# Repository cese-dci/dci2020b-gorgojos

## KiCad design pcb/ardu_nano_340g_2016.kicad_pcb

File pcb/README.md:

Directorio “pcb” donde se colocará el proyecto Kicad.

se agregan librerias de digikey y de https://github.com/epernia/CIAA-Z3R0

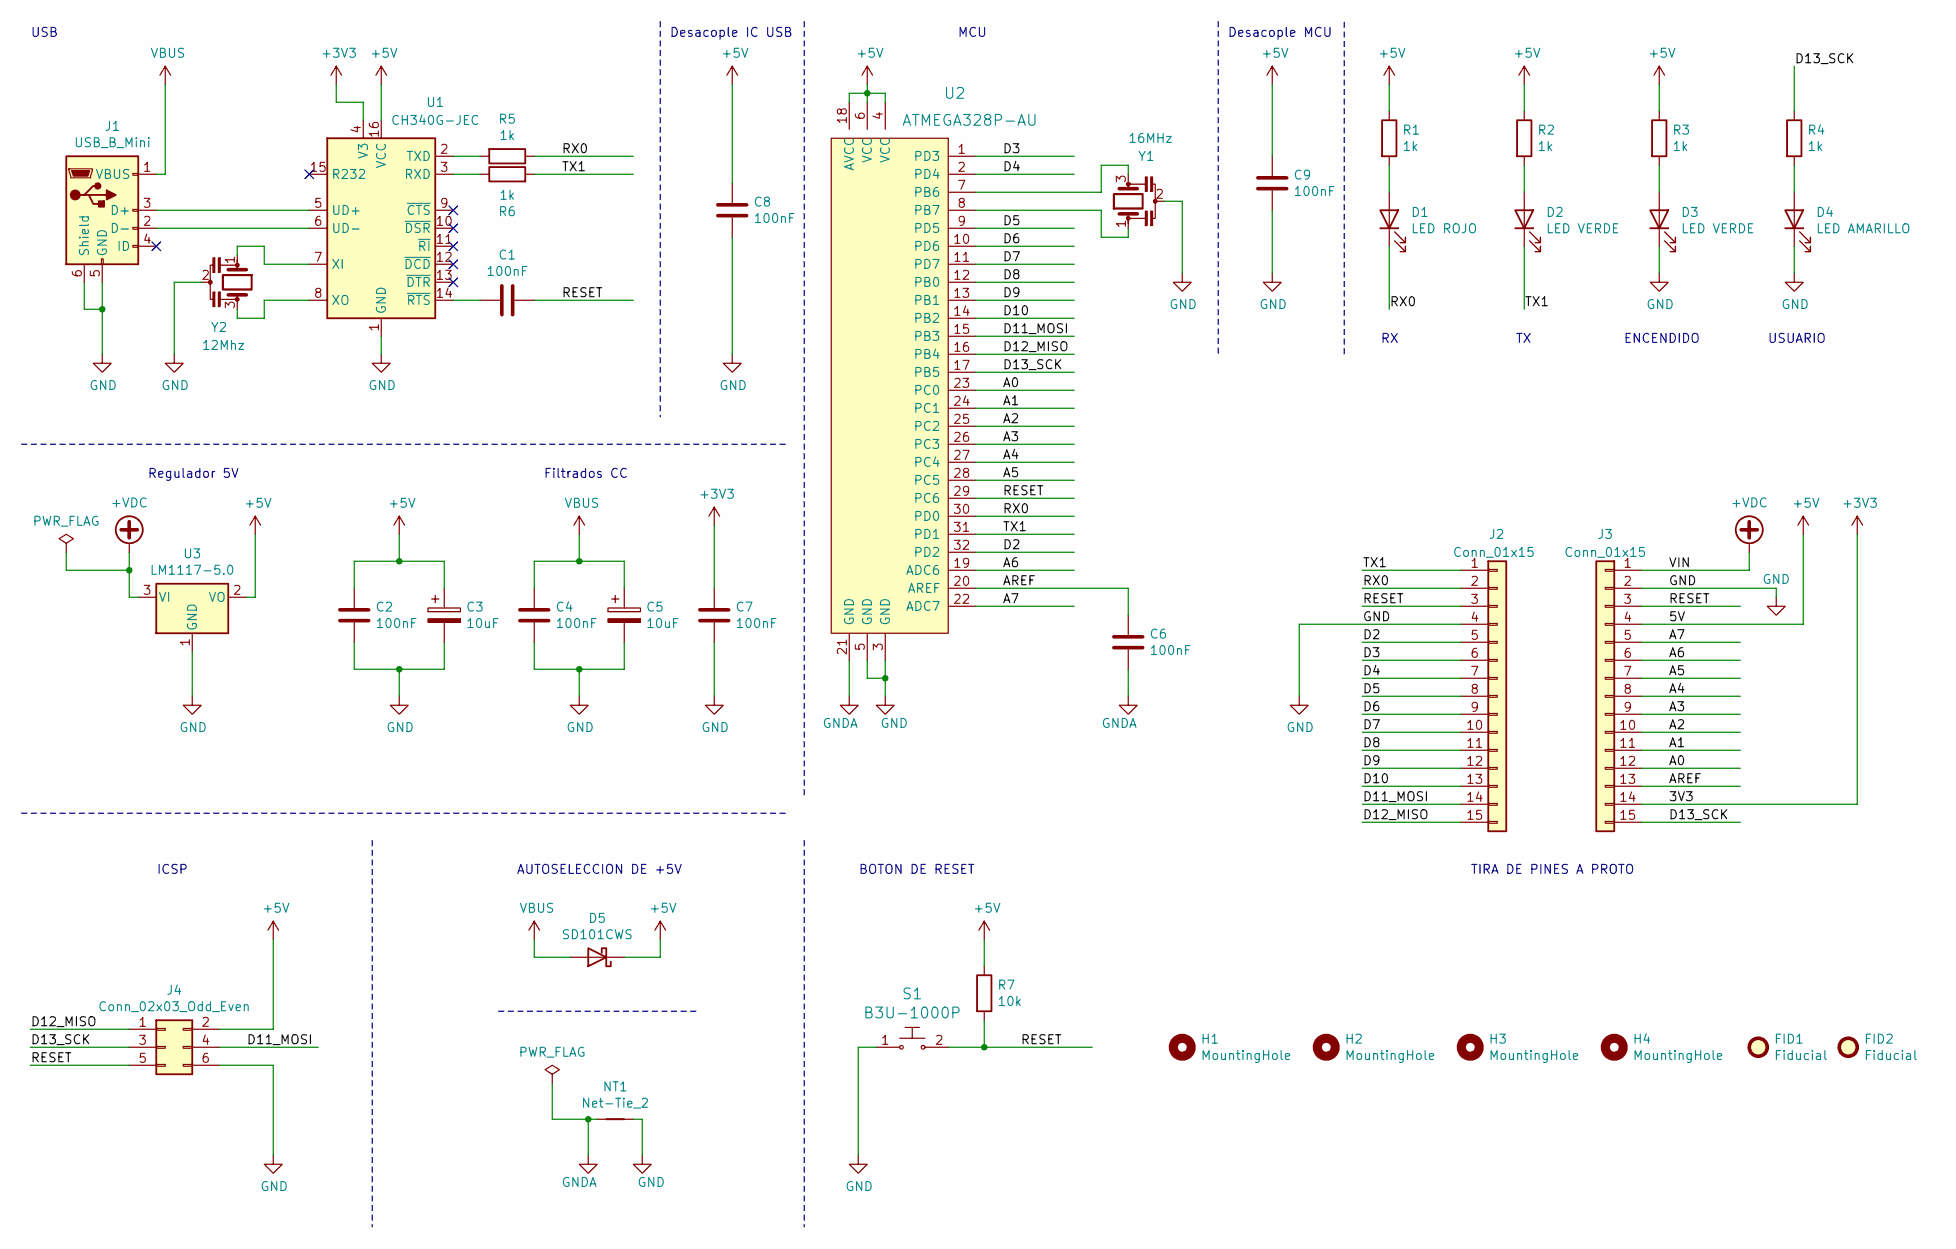
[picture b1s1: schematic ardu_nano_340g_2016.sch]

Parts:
C1, C2, C4, C6: 100nF; C_0805_2012Metric_Pad1.15x1.40mm_HandSolder; MPN CL21B104KBFXPJE; Digi-Key_PN 1276-CL21B104KBFXPJECT-ND
C3, C5: 10uF; CP_EIA-3216-18_Kemet-A_Pad1.58x1.35mm_HandSolder; Digi-Key_PN C194304
C7, C8, C9: 100nF; C_0805_2012Metric_Pad1.18x1.45mm_HandSolder; MPN CL21B104KBFXPJE; Digi-Key_PN 1276-CL21B104KBFXPJECT-ND
D1: LED ROJO; LED_0805_2012Metric_Pad1.15x1.40mm_HandSolder; MPN 150080SS75000; Digi-Key_PN 732-4985-1-ND
D2, D3: LED VERDE; LED_0805_2012Metric_Pad1.15x1.40mm_HandSolder; MPN 150080VS75000; Digi-Key_PN 732-4986-1-ND
D4: LED AMARILLO; LED_0805_2012Metric_Pad1.15x1.40mm_HandSolder; MPN 150080YS75000; Digi-Key_PN 732-4987-1-ND
D5: SD101CWS; D_SOD-323_HandSoldering; MPN SD101CWS; Digi-Key_PN C241955
FID1, FID2: Fiducial; Fiducial_1mm_Mask2mm
H1, H2: MountingHole; MountingHole_2.2mm_M2_ISO7380
H3, H4: MountingHole; MountingHole_2.2mm_M2_ISO14580
J1: USB_B_Mini; USB_Mini-B_Lumberg_2486_01_Horizontal; MPN UX60-MB-5ST; Digi-Key_PN H2959CT-ND
J2, J3: Conn_01x15; PinHeader_1x15_P2.54mm_Vertical; MPN TSW-115-07-T-S; Digi-Key_PN SAM1035-15-ND
J4: Conn_02x03_Odd_Even; PinHeader_2x03_P2.54mm_Vertical; MPN TSW-103-07-T-D; Digi-Key_PN SAM1034-03-ND
NT1: Net-Tie_2; NetTie-2_SMD_Pad0.5mm
R1, R2, R3, R4, R5, R6: 1k; R_0805_2012Metric_Pad1.15x1.40mm_HandSolder; MPN RNCP0805FTD1K00; Digi-Key_PN RNCP0805FTD1K00CT-ND
R7: 10k; R_0805_2012Metric_Pad1.15x1.40mm_HandSolder; MPN RNCP0805FTD1K00; Digi-Key_PN RNCP0805FTD1K00CT-ND
S1: B3U-1000P; Switch_Tactile_SMD_B3U-1000P; MPN B3U-1000P; Digi-Key_PN SW1020CT-ND
U1: CH340G-JEC; SOIC-16_3.9x9.9mm_P1.27mm; MPN CH340G; Digi-Key_PN C14267
U2: ATMEGA328P-AU; LQFP-32_7x7mm_P0.8mm; MPN ATMEGA328P-AU; Digi-Key_PN ATMEGA328P-AU-ND
U3: LM1117-5.0; SOT-223-3_TabPin2; MPN LM1117MP-5.0/NOPB; Digi-Key_PN LM1117MP-5.0/NOPBCT-ND
Y1: 16MHz; Resonator_SMD_muRata_CSTxExxV-3Pin_3.0x1.1mm; MPN CSTNE16M0V530000R0; Digi-Key_PN 490-17948-1-ND
Y2: 12Mhz; Resonator_SMD_muRata_CSTxExxV-3Pin_3.0x1.1mm; MPN CSTNE12M0G550000R0; Digi-Key_PN 490-17943-1-ND

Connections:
+3V3: C7.1, J3.14, U1.4 (V3)
+5V: C2.1, C3.1, C8.1, C9.1, D5.1 (K), J3.4, J4.2, R1.1, R2.1, R3.1, R7.1, U1.16 (VCC), U2.4 (VCC), U2.6 (VCC), U2.18 (AVCC), U3.2 (VO)
+VDC: J3.1, U3.3 (VI)
/A0: J3.12, U2.23 (PC0)
/A1: J3.11, U2.24 (PC1)
/A2: J3.10, U2.25 (PC2)
/A3: J3.9, U2.26 (PC3)
/A4: J3.8, U2.27 (PC4)
/A5: J3.7, U2.28 (PC5)
/A6: J3.6, U2.19 (ADC6)
/A7: J3.5, U2.22 (ADC7)
/AREF: C6.1, J3.13, U2.20 (AREF)
/D2: J2.5, U2.32 (PD2)
/D3: J2.6, U2.1 (PD3)
/D4: J2.7, U2.2 (PD4)
/D5: J2.8, U2.9 (PD5)
/D6: J2.9, U2.10 (PD6)
/D7: J2.10, U2.11 (PD7)
/D8: J2.11, U2.12 (PB0)
/D9: J2.12, U2.13 (PB1)
/D10: J2.13, U2.14 (PB2)
/D11_MOSI: J2.14, J4.4, U2.15 (PB3)
/D12_MISO: J2.15, J4.1, U2.16 (PB4)
/D13_SCK: J3.15, J4.3, R4.1, U2.17 (PB5)
/RESET: C1.1, J2.3, J3.3, J4.5, R7.2, S1.2, U2.29 (PC6)
/RX0: D1.1 (K), J2.2, R5.1, U2.30 (PD0)
/TX1: D2.1 (K), J2.1, R6.2, U2.31 (PD1)
GND: C2.2, C3.2, C4.2, C5.2, C7.2, C8.2, C9.2, D3.1 (K), D4.1 (K), J1.5 (GND), J1.6 (Shield), J2.4, J3.2, J4.6, NT1.2, S1.1, U1.1 (GND), U2.3 (GND), U2.5 (GND), U3.1 (GND), Y1.2, Y2.2
GNDA: C6.2, NT1.1, U2.21 (GND)
unnamed: C1.2, U1.14 (~RTS)
unnamed: D1.2 (A), R1.2
unnamed: D2.2 (A), R2.2
unnamed: D3.2 (A), R3.2
unnamed: D4.2 (A), R4.2
unnamed: J1.2 (D-), U1.6 (UD-)
unnamed: J1.3 (D+), U1.5 (UD+)
unnamed: R5.2, U1.2 (TXD)
unnamed: R6.1, U1.3 (RXD)
unnamed: U1.7 (XI), Y2.1
unnamed: U1.8 (XO), Y2.3
unnamed: U2.7 (PB6), Y1.3
unnamed: U2.8 (PB7), Y1.1
VBUS: C4.1, C5.1, D5.2 (A), J1.1 (VBUS)

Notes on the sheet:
AUTOSELECCION DE +5V
ICSP
USB
Regulador 5V
Filtrados CC
BOTON DE RESET
MCU
ENCENDIDO
USUARIO
TIRA DE PINES A PROTO
Desacople IC USB
Desacople MCU

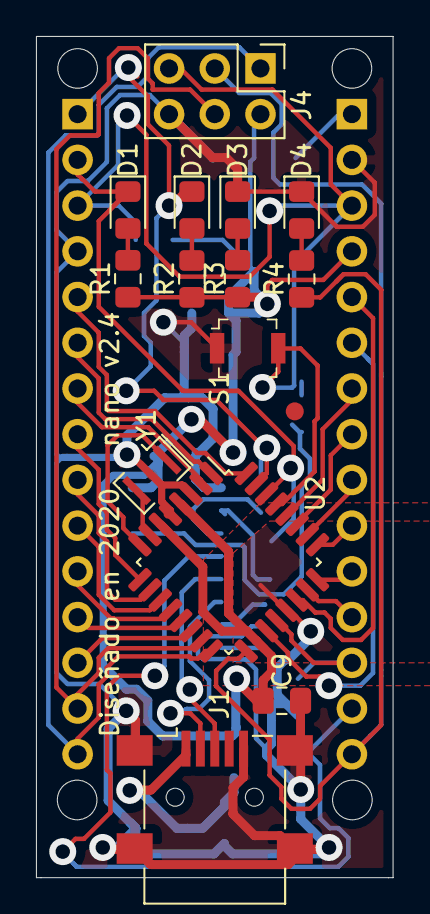
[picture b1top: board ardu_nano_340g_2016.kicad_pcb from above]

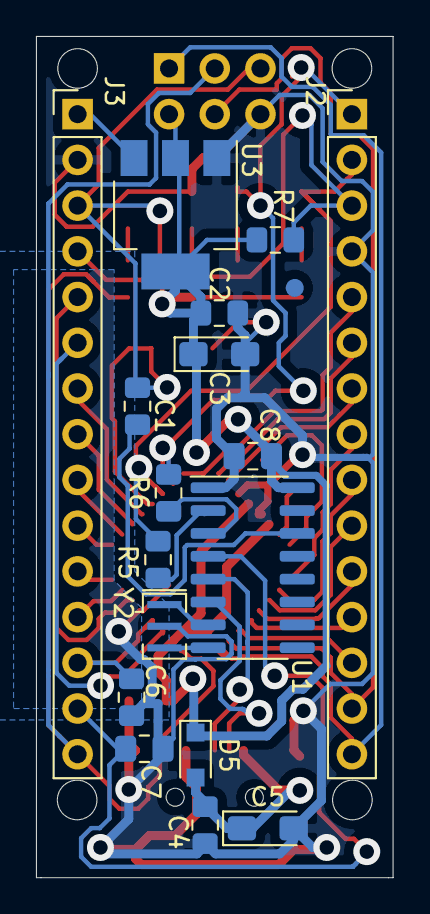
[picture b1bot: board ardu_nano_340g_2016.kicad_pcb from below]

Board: 2 copper layers, 19.8 x 46.7 mm, 38 parts (19 on the bottom side), 43 nets.

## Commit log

2020-10-02 add folders doc, info, pcb, 3dshapes and README.md
2020-10-14 componentes colocados en esquematico
2020-10-14 se agregaron valores y codigos de compra de todas las partes
2020-10-15 asignacion de todas las huellas
2020-10-15 Se actualizo a version 2.1 porque se agrego capacitor de filtrado de 3V3
2020-10-15 primera acomodad en el PCB, faltan un par de 3D y una revision general del posicionamiento
2020-10-16 Se agregaron valores de resistencias e imagenes de placa real de referencia
2020-10-18 V2.2 Se agregó capacitor desacople IC USB y se redujo huella resonadores
2020-10-18 V2.3 Se agregó capacitor desacople MCU
2020-10-18 avances del 17/10/2020
2020-10-20 ruteado completo
2020-11-19 add especificaciones fabricante
2020-11-21 versión para fabricación casera con vias grandes

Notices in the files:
pcb/ardu_nano_340g_2016.kicad_pcb:
Licencia: CC BY-NC-SA
